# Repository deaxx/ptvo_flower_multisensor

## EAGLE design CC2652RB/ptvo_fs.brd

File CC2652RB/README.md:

### Components:
E72-2G4M05S1F - https://aliexpress.ru/item/1005006060110453.html

Cell Holder CR2450 - https://aliexpress.ru/item/33036966276.html

Micro Button Tact Switch SMD 2Pin - https://aliexpress.ru/item/1005001629364313.html

DS18B20U MSOP-8 - https://aliexpress.ru/item/32903017916.html

Quartz Oscillator 48 MHz - https://aliexpress.ru/item/1005001781710042.html

### Information:

For lower power consumption of the E72-2G4M05S1F module, it is recommended to install a quartz oscillator at 48 MHz.

With a 48 MHz quartz oscillator installed, flash the E72-2G4M05S1F module with PTVO firmware for the CC2652R chip

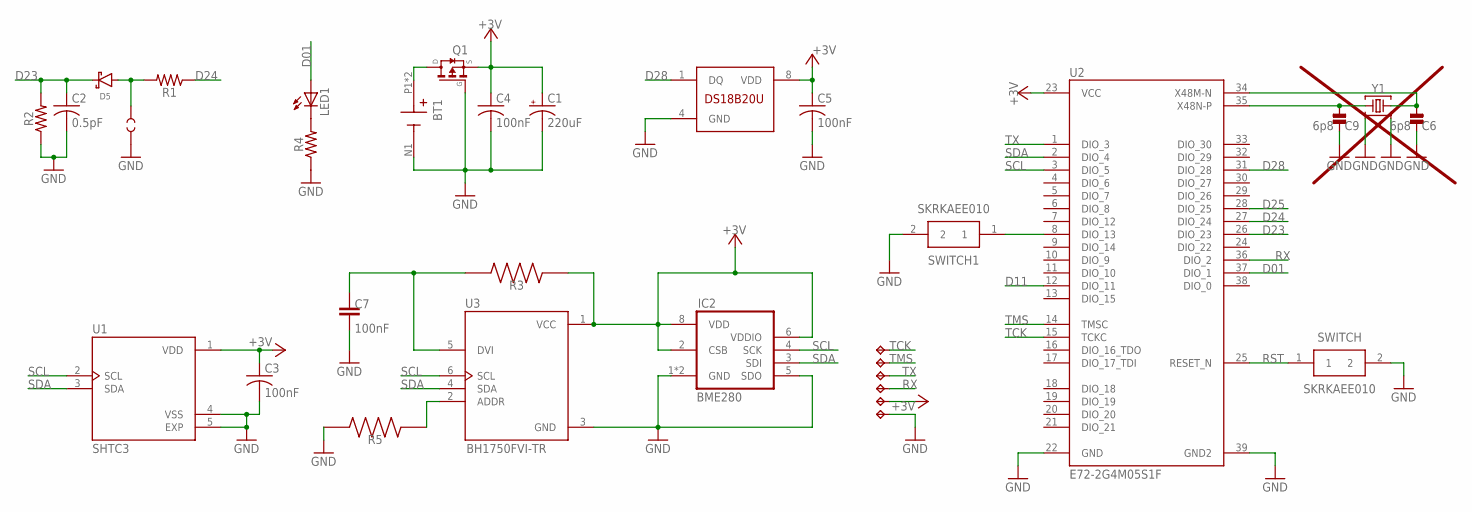
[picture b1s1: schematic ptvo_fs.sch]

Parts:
BT1: BAT-HLD-001; BAT_BAT-HLD-001
C1: 220uF; EIA7343
C2: 0.5pF; C0805
C3, C4, C5: 100nF; C0805
C6, C9: 6p8; _PKG_C_0402
C7: 100nF; CAPC1005X40N
D5: 1N4148WS; SOD-323
IC1: DS18S20USOP8; UMAX8
IC2: BME280
LED1: LEDCHIP-LED0805; CHIP-LED0805
Q1: SI2323DS; SOT23
R1: 10k; M0805
R2: 1M; M0805
R3, R5: 4.7k; RESC1005X40N
R4: 2.2k; M0805
SWITCH, SWITCH1: SKRKAEE010; SKRK
TP1, TP2: TEST-POINT2; PAD.02X.02
TP3, TP4, TP5, TP6, TP7, TP8: TPB1,27; B1,27
U1: SHTC3; SON100P200X200X80-5N
U2: E72-2G4M05S1F
U3: BH1750FVI-TR; XDCR_BH1750FVI-TR
Y1: Q22FA12800150; XTAL-4P-2016

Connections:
+3V3: C1.A (+), C3.1, C4.1, C5.1, IC1.8 (VDD), IC2.2 (CSB), IC2.6 (VDDIO), IC2.8 (VDD), Q1.2 (S), R3.1, TP6.TP, U1.1 (VDD), U2.23 (VCC), U3.1 (VCC)
D01: LED1.A, U2.37 (DIO_1)
D11: U2.12 (DIO_11)
D23: C2.1, D5.C, R2.2, U2.26 (DIO_23)
D24: R1.1, U2.27 (DIO_24)
D25: U2.28 (DIO_25)
D28: IC1.1 (DQ), U2.31 (DIO_28)
GND: BT1.N1 (-), C1.C (-), C2.2, C3.2, C4.2, C5.2, C6.1, C7.2, C9.1, IC1.4 (GND), IC2.1 (GND), IC2.5 (SDO), IC2.7 (GND), Q1.1 (G), R2.1, R4.1, R5.2, SWITCH.2, SWITCH1.2, TP2.P$1, TP7.TP, U1.4 (VSS), U1.5 (EXP), U2.22 (GND), U2.39 (GND2), U3.3 (GND), Y1.2, Y1.4
unnamed: D5.A, R1.2, TP1.P$1
unnamed: LED1.C, R4.2
unnamed: SWITCH1.1, U2.8 (DIO_13)
unnamed: BT1.P1 (+), BT1.P2 (+), Q1.3 (D)
unnamed: C6.2, U2.34 (X48M-N), Y1.3
unnamed: C7.1, R3.2, U3.5 (DVI)
unnamed: R5.1, U3.2 (ADDR)
unnamed: C9.2, U2.35 (X48N-P), Y1.1
RST: SWITCH.1, U2.25 (RESET_N)
RX: TP5.TP, U2.36 (DIO_2)
SCL: IC2.4 (SCK), U1.2 (SCL), U2.3 (DIO_5), U3.6 (SCL)
SDA: IC2.3 (SDI), U1.3 (SDA), U2.2 (DIO_4), U3.4 (SDA)
TCK: TP8.TP, U2.15 (TCKC)
TMS: TP3.TP, U2.14 (TMSC)
TX: TP4.TP, U2.1 (DIO_3)

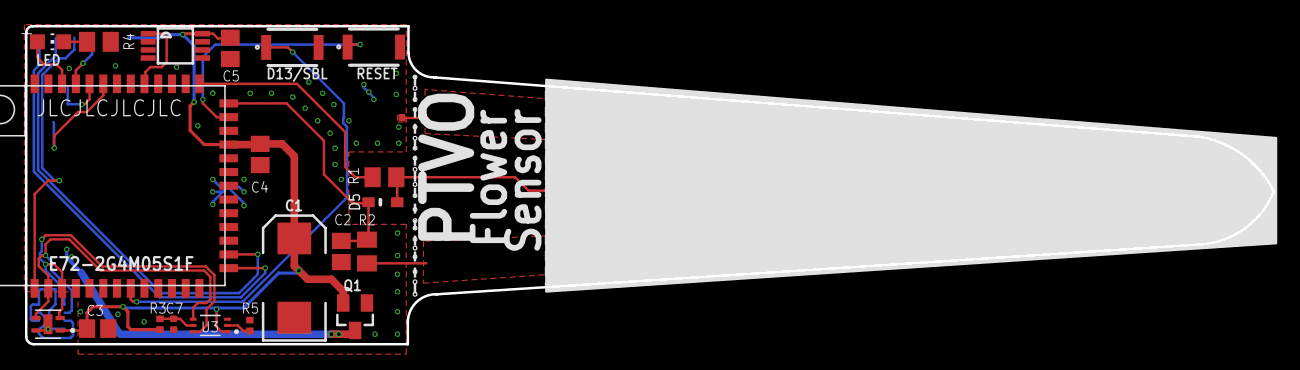
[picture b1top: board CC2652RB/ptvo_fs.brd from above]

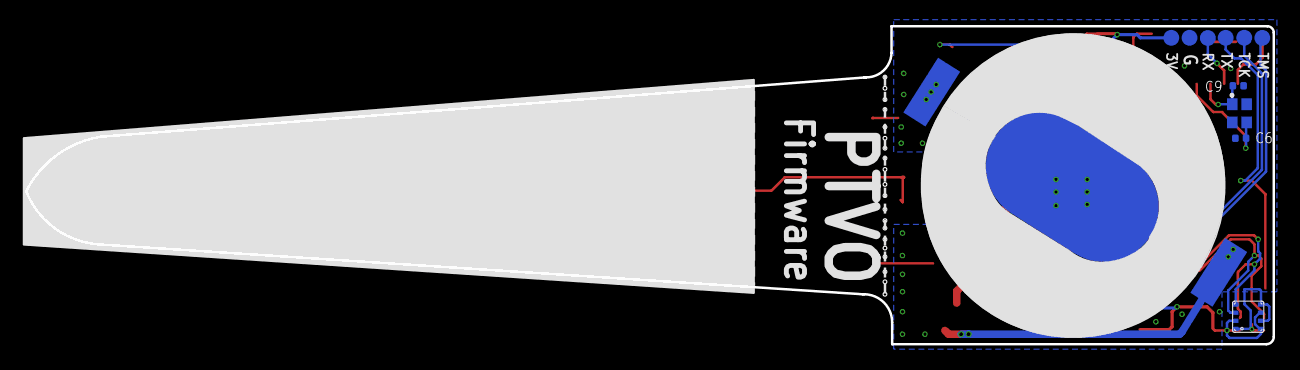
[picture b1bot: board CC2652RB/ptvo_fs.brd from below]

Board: 2 copper layers, 100.0 x 25.5 mm, 33 parts (11 on the bottom side), 21 nets.

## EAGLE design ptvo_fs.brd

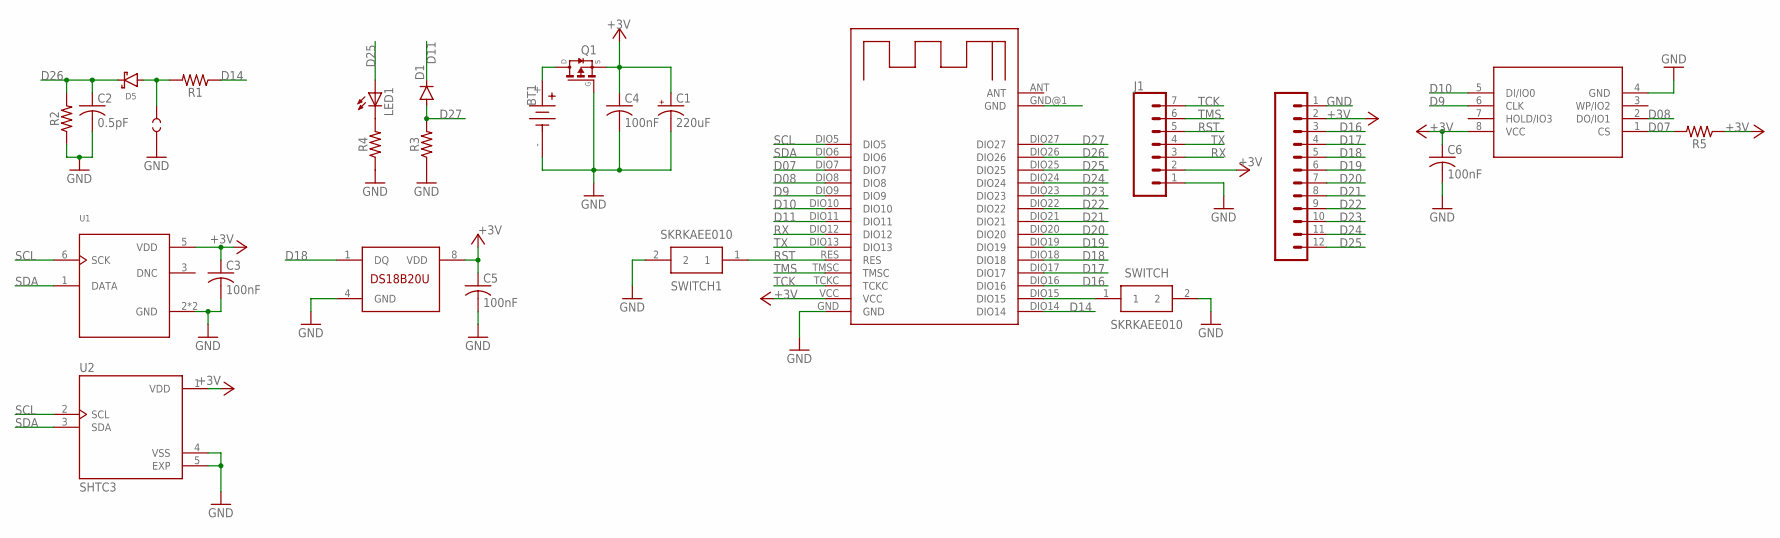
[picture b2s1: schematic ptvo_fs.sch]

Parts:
BT1: BH2AAAPC; BAT_BH2AAAPC
C1: 220uF; EIA7343
C2: 0.5pF; C0805
C3, C4, C5, C6: 100nF; C0805
D1: PTSMD3528; DO214BA
D5: 1N4148WS; SOD-323
IC1: DS18S20USOP8; UMAX8
J1, J2: CONN_051.27MM; 1X05_1.27MM
LED1: LEDCHIP-LED0805; CHIP-LED0805
Q1: SI2323DS; SOT23
R1, R3: 10k; M0805
R2: 1M; M0805
R4, R5: 2.2k; M0805
SWITCH, SWITCH1: SKRKAEE010; SKRK
TP1, TP2: TEST-POINT2; PAD.02X.02
U1: HTU21D; QFN100P300X300X100-7N
U2: SHTC3; SON100P200X200X80-5N
U$1: RF-BM-2652P2
U$2: IS25LP080D; SO-8

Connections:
+3V3: C1.A (+), C3.1, C4.1, C5.1, C6.1, IC1.8 (VDD), J1.2, J2.2, Q1.2 (S), R5.1, U1.5 (VDD), U2.1 (VDD), U$1.VCC, U$2.8 (VCC)
D07: R5.2, U$1.DIO7, U$2.1 (CS)
D08: U$1.DIO8, U$2.2 (DO/IO1)
D9: U$1.DIO9, U$2.6 (CLK)
D10: U$1.DIO10, U$2.5 (DI/IO0)
D11: D1.C, U$1.DIO11
D14: R1.1, U$1.DIO14
D16: J2.3, U$1.DIO16
D17: J2.4, U$1.DIO17
D18: IC1.1 (DQ), J2.5, U$1.DIO18
D19: J2.6, U$1.DIO19
D20: J2.7, U$1.DIO20
D21: J2.8, U$1.DIO21
D22: J2.9, U$1.DIO22
D23: J2.10, U$1.DIO23
D24: J2.11, U$1.DIO24
D25: J2.12, LED1.A, U$1.DIO25
D26: C2.1, D5.C, R2.2, U$1.DIO26
D27: D1.A, R3.2, U$1.DIO27
GND: BT1.-, C1.C (-), C2.2, C3.2, C4.2, C5.2, C6.2, IC1.4 (GND), J1.1, J2.1, Q1.1 (G), R2.1, R3.1, R4.1, SWITCH.2, SWITCH1.2, TP2.P$1, U1.2 (GND), U1.PAD (GND), U2.4 (VSS), U2.5 (EXP), U$1.GND, U$2.4 (GND)
unnamed: D5.A, R1.2, TP1.P$1
unnamed: LED1.C, R4.2
unnamed: SWITCH.1, U$1.DIO15
unnamed: BT1.+, Q1.3 (D)
RST: J1.5, SWITCH1.1, U$1.RES
RX: J1.3, U$1.DIO12
SCL: U1.6 (SCK), U2.2 (SCL), U$1.DIO5
SDA: U1.1 (DATA), U2.3 (SDA), U$1.DIO6
TCK: J1.7, U$1.TCKC
TMS: J1.6, U$1.TMSC
TX: J1.4, U$1.DIO13

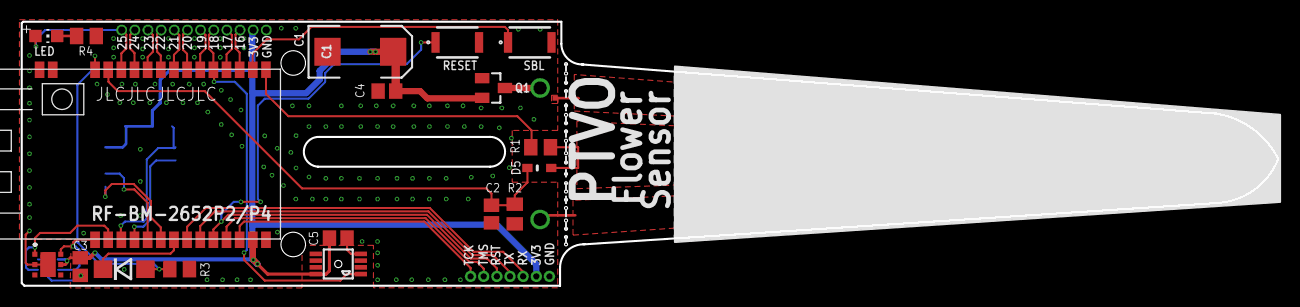
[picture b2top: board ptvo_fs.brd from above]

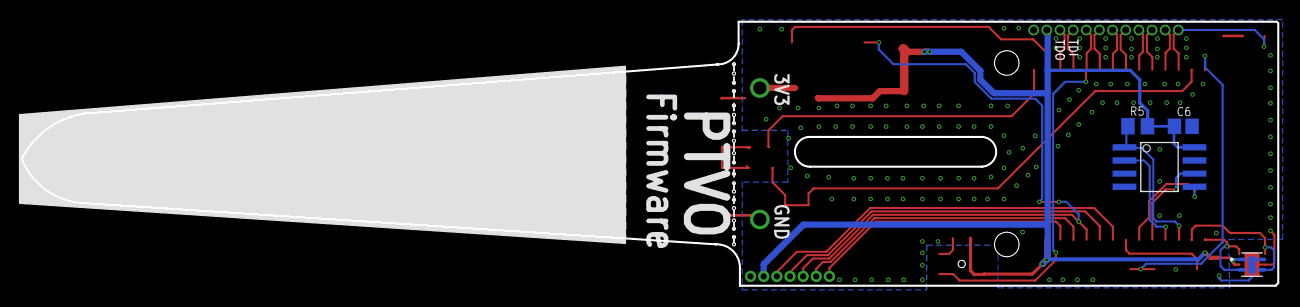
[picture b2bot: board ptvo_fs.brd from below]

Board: 2 copper layers, 121.4 x 25.5 mm, 27 parts (5 on the bottom side), 31 nets.

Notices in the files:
parts and their libraries:
SparkFun-Capacitors: Licensing: Creative Commons ShareAlike 4.0 International - https://creativecommons.org/licenses/by-sa/4.0
